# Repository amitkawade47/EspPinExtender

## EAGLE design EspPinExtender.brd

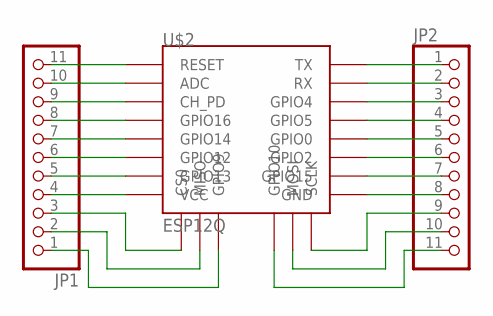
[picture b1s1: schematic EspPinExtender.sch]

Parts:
JP1, JP2: PINHD-1X11; 1X11
U$2: ESP12Q

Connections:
unnamed: JP1.4, U$2.VCC
unnamed: JP1.5, U$2.GPIO13
unnamed: JP1.6, U$2.GPIO12
unnamed: JP1.7, U$2.GPIO14
unnamed: JP1.8, U$2.GPIO16
unnamed: JP1.3, U$2.CS0
unnamed: JP1.2, U$2.MISO
unnamed: JP1.1, U$2.GPIO9
unnamed: JP1.9, U$2.CH_PD
unnamed: JP1.10, U$2.ADC
unnamed: JP1.11, U$2.RESET
unnamed: JP2.1, U$2.TX
unnamed: JP2.2, U$2.RX
unnamed: JP2.9, U$2.SCLK
unnamed: JP2.10, U$2.MOSI
unnamed: JP2.11, U$2.GPIO10
unnamed: JP2.3, U$2.GPIO4
unnamed: JP2.4, U$2.GPIO5
unnamed: JP2.5, U$2.GPIO0
unnamed: JP2.6, U$2.GPIO2
unnamed: JP2.7, U$2.GPIO15
unnamed: JP2.8, U$2.GND

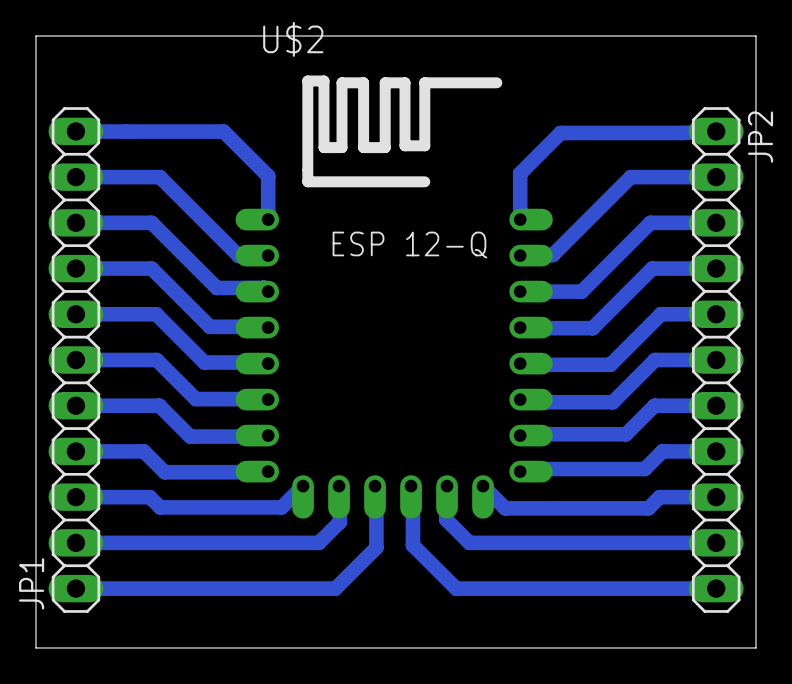
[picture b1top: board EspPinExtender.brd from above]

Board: 2 copper layers, 40.0 x 34.0 mm, 3 parts (0 on the bottom side), 22 nets.

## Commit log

2018-02-22 SCH and BRD
    board designed to fit on breadboard.
2018-02-22 brd and comp pdf
    brd layout with component pdf added
